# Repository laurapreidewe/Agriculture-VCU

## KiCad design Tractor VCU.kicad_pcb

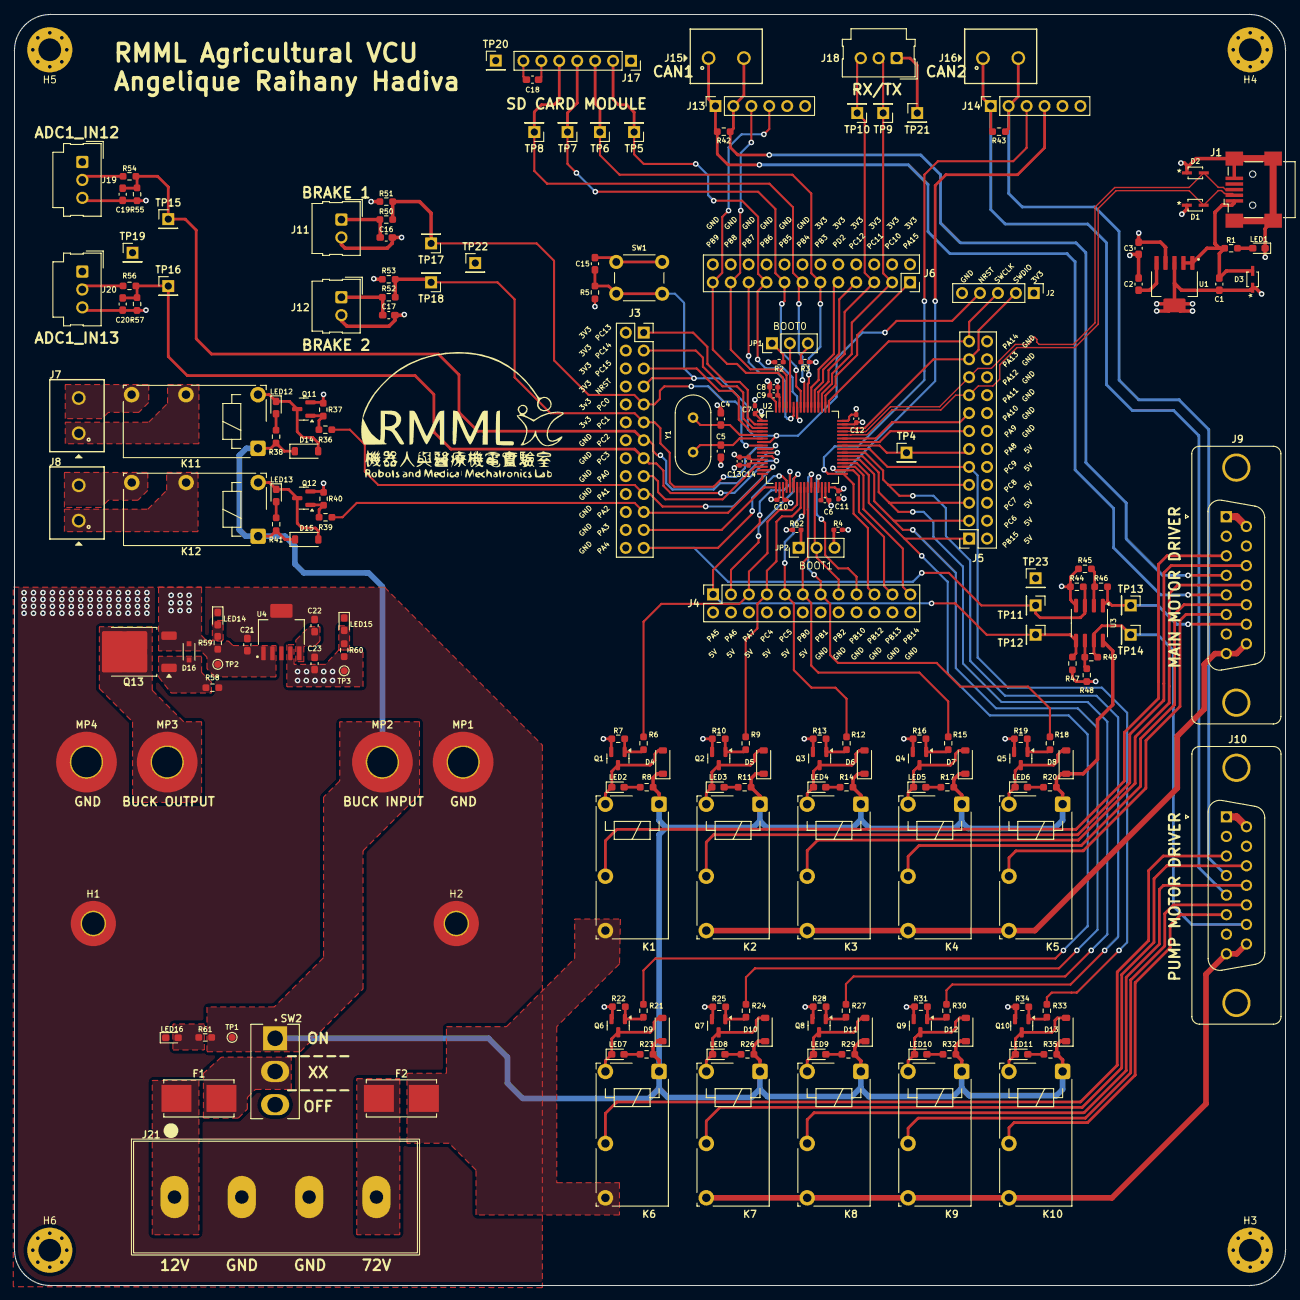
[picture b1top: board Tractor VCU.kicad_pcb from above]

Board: 4 copper layers, 180.0 x 180.0 mm, 207 parts (0 on the bottom side), 140 nets.

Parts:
C1, C3, C21, C23: 1u; C_0603_1608Metric_Pad1.08x0.95mm_HandSolder
C2, C22: 0.01u; C_0603_1608Metric_Pad1.08x0.95mm_HandSolder
C4, C5: 22p; C_0603_1608Metric_Pad1.08x0.95mm_HandSolder
C6, C13: 1u; C_0402_1005Metric_Pad0.74x0.62mm_HandSolder
C7, C9, C10, C11, C12, C14: 100n; C_0402_1005Metric_Pad0.74x0.62mm_HandSolder
C8: 10u; C_0402_1005Metric_Pad0.74x0.62mm_HandSolder
C15, C16, C17, C18, C19, C20: 100n; C_0603_1608Metric_Pad1.08x0.95mm_HandSolder
D1, D2, D3: DESD5V0U1BA-7; SOD323-L_DIO-M
D4, D5, D6, D7, D8, D9, D10, D11, D12, D13, D14, D15: 1N4148; D_SOD-123
D16: PLZ4V7C-G3/H; CR_PLZ5V1C_VIS-L
F1, F2: 0154010.DR; Fuseholder_Littelfuse_Nano2_154x
H1: BUCK1PAD1; MountingHole_3.2mm_M3_Pad_TopBottom
H2: BUCK1PAD2; MountingHole_3.2mm_M3_Pad_TopBottom
H3, H4, H5, H6: MOUNTINGHOLE; MountingHole_3.2mm_M3_Pad_Via
J1: USB_B_Mini; USB_Mini-B_Wuerth_65100516121_Horizontal
J2: ST-LINKV2; PinHeader_1x05_P2.54mm_Vertical
J3: Conn_02x13_Odd_Even; PinSocket_2x13_P2.54mm_Vertical
J4, J5, J6: Conn_02x12_Odd_Even; PinSocket_2x12_P2.54mm_Vertical
J7: RELAY1_EXTERNAL; Wuerth 691137710002_1x02
J8: RELAY2_EXTERNAL; Wuerth 691137710002_1x02
J9: MAIN MOTOR; DSUB-15_Female_Vertical_P2.77x2.84mm_MountingHoles
J10: PUMP MOTOR; DSUB-15_Female_Vertical_P2.77x2.84mm_MountingHoles
J11: BRAKE1; Molex_SL_171971-0002_1x02_P2.54mm_Vertical
J12: BRAKE2; Molex_SL_171971-0002_1x02_P2.54mm_Vertical
J13, J14: CAN_MCP2551; PinSocket_1x06_P2.54mm_Vertical
J15: CAN1 TEST; Wuerth 691137710002_1x02
J16: CAN2 TEST; Wuerth 691137710002_1x02
J17: SD CARD MODULE; PinSocket_1x07_P2.54mm_Vertical
J18: USART; Molex_SL_171971-0003_1x03_P2.54mm_Vertical
J19: ADC1_IN12; Molex_SL_171971-0003_1x03_P2.54mm_Vertical
J20: ADC1_IN13; Molex_SL_171971-0003_1x03_P2.54mm_Vertical
J21: INPUT; Molex_38720-6304
JP1: BOOT0MODE; PinHeader_1x03_P2.54mm_Vertical
JP2: BOOT1MODE; PinHeader_1x03_P2.54mm_Vertical
K1, K2, K3, K4, K5: RELAY_MM; Relay_SPST_Fujitsu_JY-12H-K
K6, K7, K8, K9, K10: RELAY_PM; Relay_SPST_Fujitsu_JY-12H-K
K11, K12: RELAY_EX; Relay_SPST_Fujitsu_JY-12H-K
LED1, LED2, LED3, LED4, LED5, LED6, LED7, LED8, LED9, LED10, LED11, LED12, LED13, LED14, LED15, LED16: LED; LED_0603_1608Metric_Pad1.05x0.95mm_HandSolder
MP1, MP2, MP3, MP4: BUCK; MountingHole_4.3mm_M4_Pad_TopBottom
Q1, Q2, Q3, Q4, Q5, Q6, Q7, Q8, Q9, Q10, Q11, Q12: BC846; SOT-23
Q13: GT6K2P10KH; TO-252-2
R1, R59: 300; R_0603_1608Metric_Pad0.98x0.95mm_HandSolder
R2, R3, R4, R62: 10k; R_0402_1005Metric_Pad0.72x0.64mm_HandSolder
R5, R6, R7, R9, R10, R12, R13, R15, R16, R18, R19, R21, R22, R24, R25, R27, R28, R30, R31, R33, R34, R36, R37, R39, R40, R44, R45, R47, R48, R51, R53, R55, R57: 10k; R_0603_1608Metric_Pad0.98x0.95mm_HandSolder
R8, R11, R14, R17, R20, R23, R26, R29, R32, R35, R38, R41, R61: 1k; R_0603_1608Metric_Pad0.98x0.95mm_HandSolder
R42, R43: 120; R_0603_1608Metric_Pad0.98x0.95mm_HandSolder
R46, R49, R54, R56: 5k1; R_0603_1608Metric_Pad0.98x0.95mm_HandSolder
R50, R52, R60: 100; R_0603_1608Metric_Pad0.98x0.95mm_HandSolder
R58: 470; R_0603_1608Metric_Pad0.98x0.95mm_HandSolder
SW1: SW_SPST; SW_PUSH_6mm
SW2: SW_SPDT; SW_500SSP1S1M2REA
TP1: 12V; TestPoint_Pad_D1.0mm
TP2: 5V; TestPoint_Pad_D1.0mm
TP3: 3V3; TestPoint_Pad_D1.0mm
TP4, TP5, TP6, TP7, TP8, TP9, TP10, TP11, TP12, TP13, TP14, TP15, TP16, TP17, TP18: TestPoint; PinHeader_1x01_P2.54mm_Vertical
TP19, TP20, TP21, TP22, TP23: GND; PinHeader_1x01_P2.54mm_Vertical
U1, U4: TPS79533DCQ; SOT127P706X180-6N
U2: STM32F446RETx; LQFP-64_10x10mm_P0.5mm
U3: LM358; SOIC-8_3.9x4.9mm_P1.27mm
Y1: 8.192MHz; Crystal_HC49-U_Vertical

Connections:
5_BUCK: MP3.1, Q13.2 (D)
+3V3: C3.1, C7.1, C8.1, C9.1, C10.1, C11.1, C12.1, C13.1, C14.1, C23.1, J2.1, J3.2, J3.4, J3.6, J3.8, J3.10, J3.12, J6.2, J6.4, J6.6, J6.8, J6.10, J6.12, R2.2, R5.1, R51.1, R53.1, R60.1, R62.2, TP3.1, U1.4 (OUT), U2.1 (VBAT), U2.13 (VDDA), U2.19 (VDD), U2.32 (VDD), U2.48 (VDD), U2.64 (VDD), U4.4 (OUT)
+5V: C18.1, C21.1, D16.1 (K), J4.2, J4.4, J4.6, J4.8, J4.10, J4.12, J5.2, J5.4, J5.6, J5.8, J5.10, J5.12, J13.6, J14.6, J17.6, J19.1, J20.1, Q13.3 (S), R59.1, TP2.1, U4.1 (EN), U4.2 (IN)
+12V: D4.1 (K), D5.1 (K), D6.1 (K), D7.1 (K), D8.1 (K), D9.1 (K), D10.1 (K), D11.1 (K), D12.1 (K), D13.1 (K), D14.1 (K), D15.1 (K), K1.8, K2.8, K3.8, K4.8, K5.8, K6.8, K7.8, K8.8, K9.8, K10.8, K11.8, K12.8, MP2.1, R8.2, R11.2, R14.2, R17.2, R20.2, R23.2, R26.2, R29.2, R32.2, R35.2, R38.2, R41.2, R61.1, SW2.1 (A), TP1.1, U3.8 (V+)
/DRIVER & CONNECTOR/ADC1_IN12: C19.1, J3.13, R54.2, R55.1, TP15.1, U2.10 (PC2)
/DRIVER & CONNECTOR/ADC1_IN13: C20.1, J3.15, R56.2, R57.1, TP16.1, U2.11 (PC3)
/DRIVER & CONNECTOR/BRAKE1_IN: J3.9, R50.2, R51.2, TP17.1, U2.8 (PC0)
/DRIVER & CONNECTOR/BRAKE1_SWITCH: C16.1, J11.1, R50.1
/DRIVER & CONNECTOR/BRAKE2_IN: J3.11, R52.2, R53.2, TP18.1, U2.9 (PC1)
/DRIVER & CONNECTOR/BRAKE2_SWITCH: C17.1, J12.1, R52.1
/DRIVER & CONNECTOR/DAC1_OUT: J3.25, R44.1, TP11.1, U2.20 (PA4), U3.3 (+)
/DRIVER & CONNECTOR/DAC2_OUT: J4.1, R47.1, TP12.1, U2.21 (PA5), U3.5 (+)
/DRIVER & CONNECTOR/DRIVER_MAIN1: J9.3, K1.13
/DRIVER & CONNECTOR/DRIVER_MAIN2: J9.11 (P111), K2.13
/DRIVER & CONNECTOR/DRIVER_MAIN3: J9.12, K3.13
/DRIVER & CONNECTOR/DRIVER_MAIN4: J9.13, K4.13
/DRIVER & CONNECTOR/DRIVER_MAIN5: J9.6, K5.13
/DRIVER & CONNECTOR/DRIVER_PUMP1: J10.3, K6.13
/DRIVER & CONNECTOR/DRIVER_PUMP2: J10.11 (P111), K7.13
/DRIVER & CONNECTOR/DRIVER_PUMP3: J10.12, K8.13
/DRIVER & CONNECTOR/DRIVER_PUMP4: J10.13, K9.13
/DRIVER & CONNECTOR/DRIVER_PUMP5: J10.6, K10.13
/DRIVER & CONNECTOR/SPI1_CS: J6.17, J17.2, TP5.1, U2.58 (PB6)
/DRIVER & CONNECTOR/SPI1_MISO: J6.13, J17.5, TP8.1, U2.56 (PB4)
/DRIVER & CONNECTOR/SPI1_MOSI: J6.15, J17.4, TP7.1, U2.57 (PB5)
/DRIVER & CONNECTOR/SPI1_SCK: J6.11, J17.3, TP6.1, U2.55 (PB3)
/DRIVER & CONNECTOR/USART3_RX: J6.5, J18.3, TP10.1, U2.52 (PC11)
/DRIVER & CONNECTOR/USART3_TX: J6.3, J18.2, TP9.1, U2.51 (PC10)
/POWER SUPPLY/72V: F2.2, K1.16, K6.16
/RELAY/COM_EX1: J7.2, K11.16
/RELAY/COM_EX2: J8.2, K12.16
/RELAY/NO_EX1: J7.1, K11.13
/RELAY/NO_EX2: J8.1, K12.13
/STM32/BOOT0: JP1.2, U2.60 (BOOT0)
/STM32/PA1: J3.19, R36.1, U2.15 (PA1)
/STM32/PA2: J3.21, R39.1, U2.16 (PA2)
/STM32/PA7: J4.5, R6.1, U2.23 (PA7)
/STM32/PB0: J4.11, R15.1, U2.26 (PB0)
/STM32/PB1: J4.13, R18.1, U2.27 (PB1)
/STM32/PB8: J6.21, J13.3, U2.61 (PB8)
/STM32/PB9: J6.23, J13.4, U2.62 (PB9)
/STM32/PB12: J4.19, J14.3, U2.33 (PB12)
/STM32/PB13: J4.21, J14.4, U2.34 (PB13)
/STM32/PB15: J5.1, R21.1, U2.36 (PB15)
/STM32/PC4: J4.7, R9.1, U2.24 (PC4)
/STM32/PC5: J4.9, R12.1, U2.25 (PC5)
/STM32/PC6: J5.3, R24.1, U2.37 (PC6)
/STM32/PC7: J5.5, R27.1, U2.38 (PC7)
/STM32/PC8: J5.7, R30.1, U2.39 (PC8)
/STM32/PC9: J5.9, R33.1, U2.40 (PC9)
/STM32/VBUS: C1.1, D3.2, J1.1 (VBUS), R1.1, U1.1 (EN), U1.2 (IN)
CAN1_N: J9.5, J13.1, J15.1, R42.1
CAN1_P: J9.4, J13.2, J15.2, R42.2
CAN2_N: J10.5, J14.1, J16.1, R43.1
CAN2_P: J10.4, J14.2, J16.2, R43.2
GND: C1.2, C2.2, C3.2, C4.2, C5.2, C6.2, C7.2, C8.2, C9.2, C10.2, C11.2, C12.2, C13.2, C14.2, C15.2, C16.2, C17.2, C18.2, C19.2, C20.2, C21.2, C22.2, C23.2, D1.1, D2.1, D3.1, H1.1, H2.1, J1.5 (GND), J1.6 (Shield), J2.5, J3.14, J3.16, J3.18, J3.20, J3.22, J3.24, J3.26, J4.14, J4.16, J4.18, J4.20, J4.22, J4.24, J5.14, J5.16, J5.18, J5.20, J5.22, J5.24, J6.14, J6.16, J6.18, J6.20, J6.22, J6.24, J9.0 (PAD), J10.0 (PAD), J11.2, J12.2, J13.5, J14.5, J17.7, J18.1, J19.3, J20.3, J21.2, J21.3, LED1.1 (K), LED14.1 (K), LED15.1 (K), LED16.1 (K), MP1.1, MP4.1, Q1.2 (E), Q2.2 (E), Q3.2 (E), Q4.2 (E), Q5.2 (E), Q6.2 (E), Q7.2 (E), Q8.2 (E), Q9.2 (E), Q10.2 (E), Q11.2 (E), Q12.2 (E), R3.2, R4.2, R7.2, R10.2, R13.2, R16.2, R19.2, R22.2, R25.2, R28.2, R31.2, R34.2, R37.2, R40.2, R44.2, R45.2, R47.2, R48.2, R55.2, R57.2, R58.2, SW1.1 (A), TP19.1, TP20.1, TP21.1, TP22.1, TP23.1, U1.3 (GND), U1.6 (GND-1), U2.12 (VSSA), U2.18 (VSS), U2.31 (VSS), U2.47 (VSS), U2.63 (VSS), U3.4 (V-), U4.3 (GND), U4.6 (GND-1)
MAIN_DGND: J9.1, J9.9
MAIN_DRIVER: J9.8, J9.15, K2.16, K3.16, K4.16, K5.16
MAIN_THROTTLE: J9.14, R46.2, TP13.1, U3.1
NRST: C15.1, J2.4, J3.7, R5.2, SW1.2 (B), U2.7 (NRST)
unnamed: D4.2 (A), K1.9, LED2.1 (K), Q1.3 (C)
unnamed: D5.2 (A), K2.9, LED3.1 (K), Q2.3 (C)
unnamed: D6.2 (A), K3.9, LED4.1 (K), Q3.3 (C)
unnamed: D7.2 (A), K4.9, LED5.1 (K), Q4.3 (C)
unnamed: D8.2 (A), K5.9, LED6.1 (K), Q5.3 (C)
unnamed: D9.2 (A), K6.9, LED7.1 (K), Q6.3 (C)
unnamed: D10.2 (A), K7.9, LED8.1 (K), Q7.3 (C)
unnamed: D11.2 (A), K8.9, LED9.1 (K), Q8.3 (C)
unnamed: D12.2 (A), K9.9, LED10.1 (K), Q9.3 (C)
unnamed: D13.2 (A), K10.9, LED11.1 (K), Q10.3 (C)
unnamed: D14.2 (A), K11.9, LED12.1 (K), Q11.3 (C)
unnamed: D15.2 (A), K12.9, LED13.1 (K), Q12.3 (C)
unnamed: D16.2 (A), Q13.1 (G), R58.1
unnamed: J19.2, R54.1
unnamed: J20.2, R56.1
unnamed: F1.1, J21.1
unnamed: F2.1, J21.4
unnamed: JP1.1, R2.1
unnamed: JP1.3, R3.1
unnamed: JP2.1, R62.1
unnamed: JP2.3, R4.1
unnamed: LED1.2 (A), R1.2
unnamed: LED2.2 (A), R8.1
unnamed: LED3.2 (A), R11.1
unnamed: LED4.2 (A), R14.1
unnamed: LED5.2 (A), R17.1
unnamed: LED6.2 (A), R20.1
unnamed: LED7.2 (A), R23.1
unnamed: LED8.2 (A), R26.1
unnamed: LED9.2 (A), R29.1
unnamed: LED10.2 (A), R32.1
unnamed: LED11.2 (A), R35.1
unnamed: LED12.2 (A), R38.1
unnamed: LED13.2 (A), R41.1
unnamed: LED14.2 (A), R59.2
unnamed: LED15.2 (A), R60.2
unnamed: LED16.2 (A), R61.2
unnamed: Q1.1 (B), R6.2, R7.1
unnamed: Q2.1 (B), R9.2, R10.1
unnamed: Q3.1 (B), R12.2, R13.1
unnamed: Q4.1 (B), R15.2, R16.1
unnamed: Q5.1 (B), R18.2, R19.1
unnamed: Q6.1 (B), R21.2, R22.1
unnamed: Q7.1 (B), R24.2, R25.1
unnamed: Q8.1 (B), R27.2, R28.1
unnamed: Q9.1 (B), R30.2, R31.1
unnamed: Q10.1 (B), R33.2, R34.1
unnamed: Q11.1 (B), R36.2, R37.1
unnamed: Q12.1 (B), R39.2, R40.1
unnamed: F1.2, SW2.2 (B)
unnamed: C2.1, U1.5 (NR\FB)
unnamed: C4.1, U2.5 (PH0), Y1.2
unnamed: C5.1, U2.6 (PH1), Y1.1
unnamed: C6.1, U2.30 (VCAP_1)
unnamed: R45.1, R46.1, U3.2 (-)
unnamed: R48.1, R49.1, U3.6 (-)
unnamed: C22.1, U4.5 (NR\FB)
PA0: J3.17, U2.14 (PA0)
PA3: J3.23, U2.17 (PA3)
PA6: J4.3, U2.22 (PA6)
PA8: J5.11, TP4.1, U2.41 (PA8)
PA9: J5.13, U2.42 (PA9)
PA10: J5.15, U2.43 (PA10)
PA13: J2.2, J5.21, U2.46 (PA13)
PA14: J2.3, J5.23, U2.49 (PA14)
PA15: J6.1, U2.50 (PA15)
PB2: J4.15, JP2.2, U2.28 (PB2)
PB7: J6.19, U2.59 (PB7)
PB10: J4.17, U2.29 (PB10)
PB14: J4.23, U2.35 (PB14)
PC12: J6.7, U2.53 (PC12)
PC13: J3.1, U2.2 (PC13)
PC14: J3.3, U2.3 (PC14)
PC15: J3.5, U2.4 (PC15)
PD2: J6.9, U2.54 (PD2)
PUMP_DGND: J10.1, J10.9
PUMP_DRIVER: J10.8, J10.15, K7.16, K8.16, K9.16, K10.16
PUMP_THROTTLE: J10.14, R49.2, TP14.1, U3.7
USB_D_N: D1.2, J1.2 (D-), J5.17, U2.44 (PA11)
USB_D_P: D2.2, J1.3 (D+), J5.19, U2.45 (PA12)

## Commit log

2025-04-19 Add files via upload
    initial commit
